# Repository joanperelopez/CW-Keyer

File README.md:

# CW keyer based on K3NG and K5BCQ work

This project was started in April 2023 based in the CW keyer of K3NG. 
I also took advantage of the good work of K5BCQ by incorporating the MEGA2560 processor. My contribution to the project has been very humble: 
  1. I have made a new schematic and PCB with SMD components. 
  2. The incorporation of a 20x4 LCD display.
  3. 3D design of a box for the entire new project.
  4. Galvanic isolation of inputs and outputs. (Optocouplers and audio transformer).
  5. Side tone regulation.
  6. USB interface.

NOTES: All documentation belongs to version 1 of the project. In this version I saw that the volume of the speaker is not very loud and I made some modifications in the 1.2 schematic that are not implemented in the current PCB. If someone wants to add these modifications they can modify the current PCB or, as is my case, add them manually.

Mechanical design made with FreeCAD.

Electronic design made with KICAD.

For download the software, setup and documentation you can go to the author's repository: https://github.com/k3ng/k3ng_cw_keyer

You can consult the K5BCQ's repository for all the information related to the modifications to use the MEGA2560: https://github.com/costonisp/CW-keyer-K3NG-K5BCQ

Feel free to copy or modify this project as long as it is not for commercial purposes.

This is what the finished keyer looks like

Exploded view of all the components of the CW keyer

Exploded view of all the components of the CW keyer

Bottom side of the main PCB

Top side of the main PCB

PCB Top view

PCB Bottom view

https://github.com/user-attachments/assets/0f88c8ea-a7e5-4cd0-9d64-bd676a6b64a1

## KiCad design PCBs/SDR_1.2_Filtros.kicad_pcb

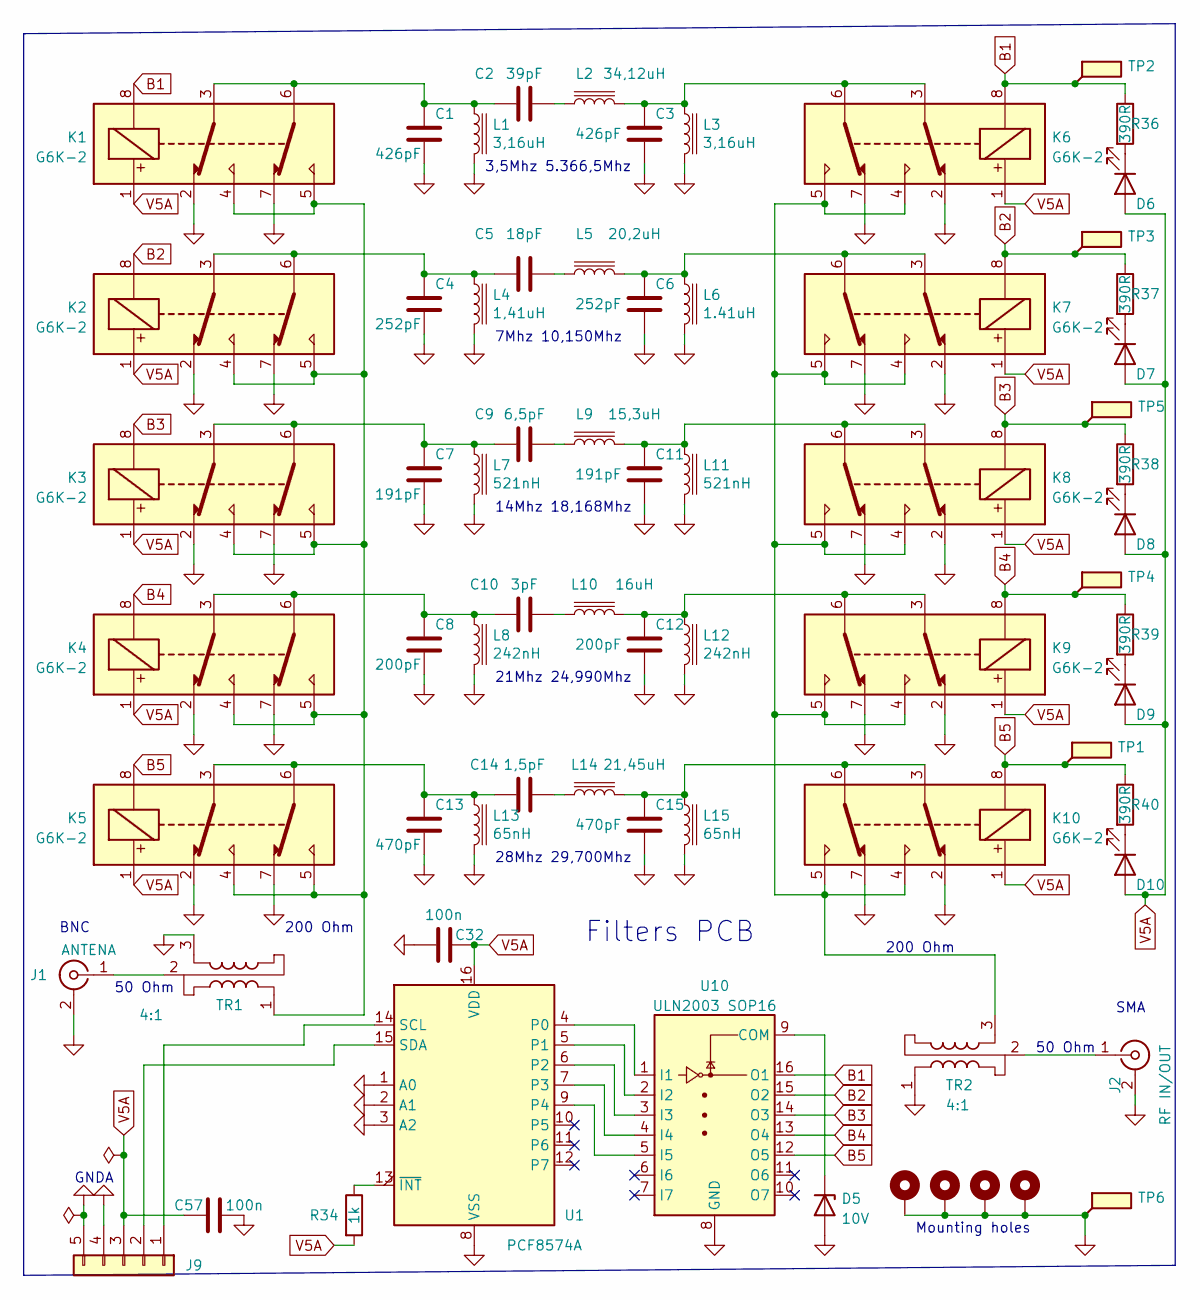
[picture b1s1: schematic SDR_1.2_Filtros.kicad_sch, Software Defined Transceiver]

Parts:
C1: 426pF; LED_0805_2012Metric_Pad1.15x1.40mm_HandSolder
C2: 39pF; C_0805_2012Metric
C3: 426pF; C_0805_2012Metric
C4, C6: 252pF; C_0805_2012Metric
C5: 18pF; C_0805_2012Metric
C7, C11: 191pF; C_0805_2012Metric
C8, C12: 200pF; C_0805_2012Metric
C9: 6,5pF; C_0805_2012Metric
C10: 3pF; C_0805_2012Metric
C13, C15: 470pF; C_0805_2012Metric
C14: 1,5pF; C_0805_2012Metric
C32, C57: 100n; C_0805_2012Metric
D5: 10V; D_SOD-123
D6, D7, D8, D9, D10: LED; LED_0805_2012Metric_Pad1.15x1.40mm_HandSolder
H1, H2, H3, H4: MountingHole_Pad; MountingHole_3.2mm_M3_Pad_TopBottom
J1: ANTENA; BNC_Amphenol_B6252HB-NPP3G-50_Horizontal
J2: RF IN/OUT; SMA_Amphenol_901-144_Vertical
J9: Conn_01x05; JST_EH_B5B-EH-A_1x05_P2.50mm_Vertical
K1, K2, K3, K4, K5, K6, K7, K8, K9, K10: G6K-2; Relay_DPDT_Omron_G6K-2F-Y
L1, L3: 3,16uH; Coil_toroid_T50_Vertical
L2: 34,12uH; Coil_toroid_T50_Vertical
L4: 1,41uH; Coil_toroid_T50_Vertical
L5: 20,2uH; Coil_toroid_T50_Vertical
L6: 1.41uH; Coil_toroid_T50_Vertical
L7, L11: 521nH; Coil_toroid_T50_Vertical
L8, L12: 242nH; Coil_toroid_T50_Vertical
L9: 15,3uH; Coil_toroid_T50_Vertical
L10: 16uH; Coil_toroid_T50_Vertical
L13, L15: 65nH; Coil_toroid_T50_Vertical
L14: 21,45uH; Coil_toroid_T50_Vertical
R34: 1k; R_0805_2012Metric_Pad1.20x1.40mm_HandSolder
R36, R37, R38, R39, R40: 390R; R_0805_2012Metric_Pad1.20x1.40mm_HandSolder
TP1, TP2, TP3, TP4, TP5, TP6: TestPoint_Flag; TestPoint_THTPad_3.0x3.0mm_Drill1.5mm
TR1, TR2: 4:1; TR_4_to_1_T50_Vertical
U1: PCF8574A; SOIC-16W_7.5x10.3mm_P1.27mm
U10: ULN2003 SOP16; SOP-16_3.9x9.9mm_P1.27mm

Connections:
B1: K1.8, K6.8, R36.1, TP2.1, U10.16 (O1)
B2: K2.8, K7.8, R37.1, TP3.1, U10.15 (O2)
B3: K3.8, K8.8, R38.1, TP5.1, U10.14 (O3)
B4: K4.8, K9.8, R39.1, TP4.1, U10.13 (O4)
B5: K5.8, K10.8, R40.1, TP1.1, U10.12 (O5)
GNDA: C1.2, C3.2, C4.2, C6.2, C7.2, C8.2, C11.2, C12.2, C13.2, C15.2, C32.1, C57.1, D5.2 (A), H1.1, H2.1, H3.1, H4.1, J1.2 (Ext), J2.2 (Ext), J9.4, J9.5, K1.2, K1.7, K2.2, K2.7, K3.2, K3.7, K4.2, K4.7, K5.2, K5.7, K6.2, K6.7, K7.2, K7.7, K8.2, K8.7, K9.2, K9.7, K10.2, K10.7, L1.2, L3.2, L4.2, L6.2, L7.2, L8.2, L11.2, L12.2, L13.2, L15.2, TP6.1, TR1.3, TR2.1, U1.1 (A0), U1.2 (A1), U1.3 (A2), U1.8 (VSS), U10.8 (GND); also elsewhere on the board
unnamed: C1.1, C2.2, K1.3, K1.6, L1.1
unnamed: C2.1, L2.1
unnamed: C3.1, K6.3, K6.6, L2.2, L3.1
unnamed: C4.1, C5.2, K2.3, K2.6, L4.1
unnamed: C5.1, L5.1
unnamed: C6.1, K7.3, K7.6, L5.2, L6.1
unnamed: C7.1, C9.2, K3.3, K3.6, L7.1
unnamed: C9.1, L9.1
unnamed: C10.1, L10.1
unnamed: C8.1, C10.2, K4.3, K4.6, L8.1
unnamed: C11.1, K8.3, K8.6, L9.2, L11.1
unnamed: C12.1, K9.3, K9.6, L10.2, L12.1
unnamed: C13.1, C14.2, K5.3, K5.6, L13.1
unnamed: C14.1, L14.1
unnamed: C15.1, K10.3, K10.6, L14.2, L15.1
unnamed: D5.1 (K), U10.9 (COM)
unnamed: D6.1 (K), R36.2
unnamed: D7.1 (K), R37.2
unnamed: D8.1 (K), R38.2
unnamed: D9.1 (K), R39.2
unnamed: D10.1 (K), R40.2
unnamed 27: J1.1 (In), TR1.2; also elsewhere on the board
unnamed: J2.1 (In), TR2.2
unnamed: J9.1, U1.14 (SCL)
unnamed: J9.2, U1.15 (SDA)
unnamed: K1.4, K1.5, K2.4, K2.5, K3.4, K3.5, K4.4, K4.5, K5.4, K5.5, TR1.1
unnamed: K6.4, K6.5, K7.4, K7.5, K8.4, K8.5, K9.4, K9.5, K10.4, K10.5, TR2.3
unnamed: R34.1, U1.13 (~INT)
unnamed: U1.4 (P0), U10.1 (I1)
unnamed: U1.5 (P1), U10.2 (I2)
unnamed: U1.6 (P2), U10.3 (I3)
unnamed: U1.7 (P3), U10.4 (I4)
unnamed: U1.9 (P4), U10.5 (I5)
V5A: C32.2, C57.2, D6.2 (A), D7.2 (A), D8.2 (A), D9.2 (A), D10.2 (A), J9.3, K1.1, K2.1, K3.1, K4.1, K5.1, K6.1, K7.1, K8.1, K9.1, K10.1, R34.2, U1.16 (VDD)

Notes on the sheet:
50 Ohm
GNDA
200 Ohm
Filters PCB
21Mhz 24,990Mhz
3,5Mhz 5.366,5Mhz
28Mhz 29,700Mhz
SMA
14Mhz 18,168Mhz
Mounting holes
BNC
7Mhz 10,150Mhz

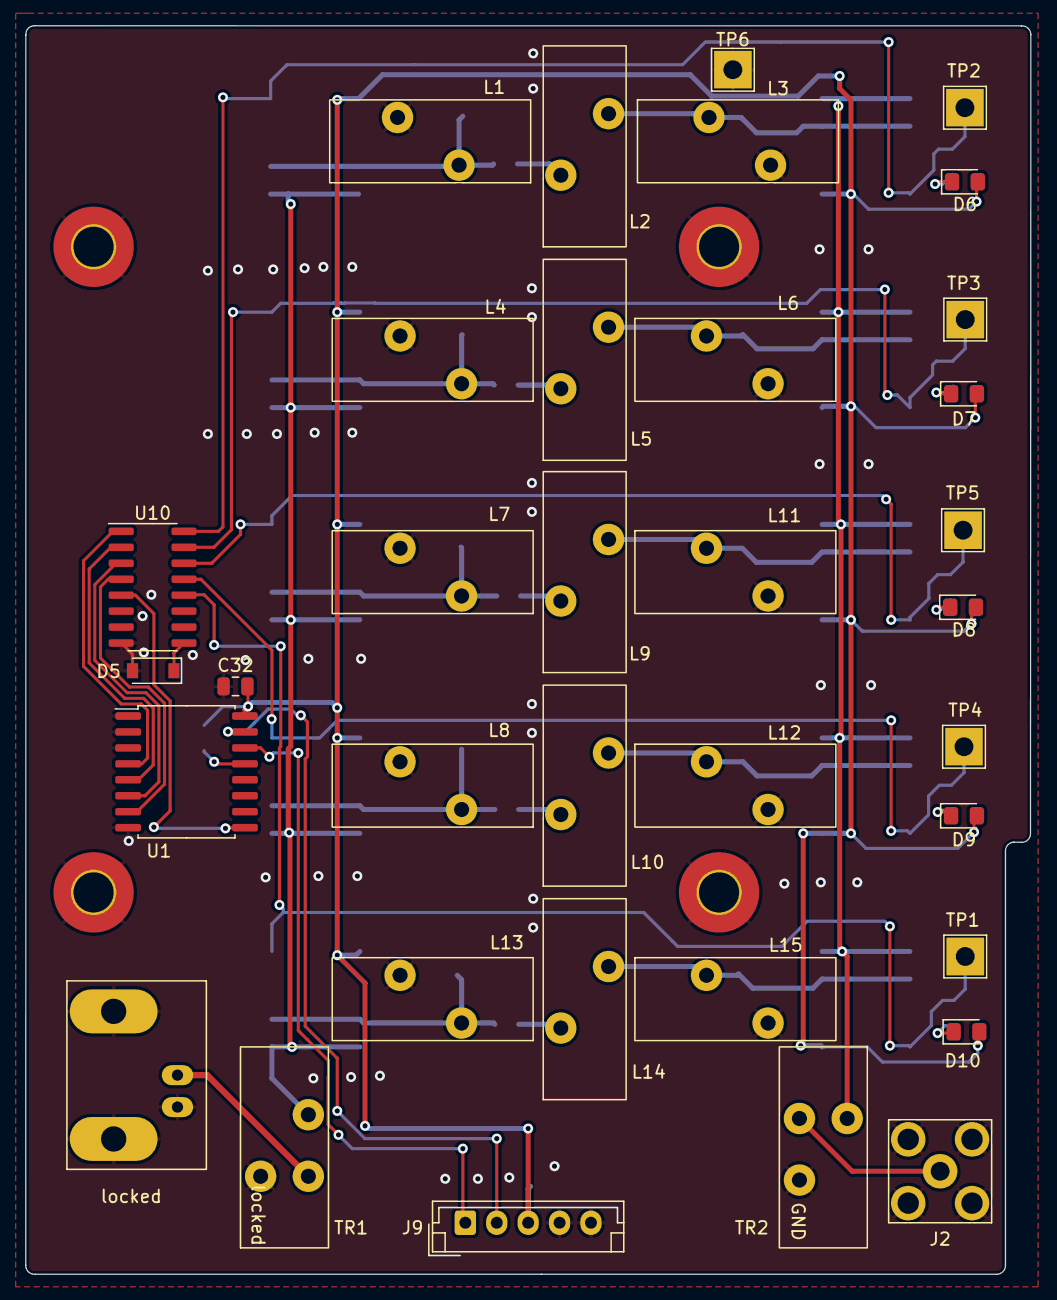
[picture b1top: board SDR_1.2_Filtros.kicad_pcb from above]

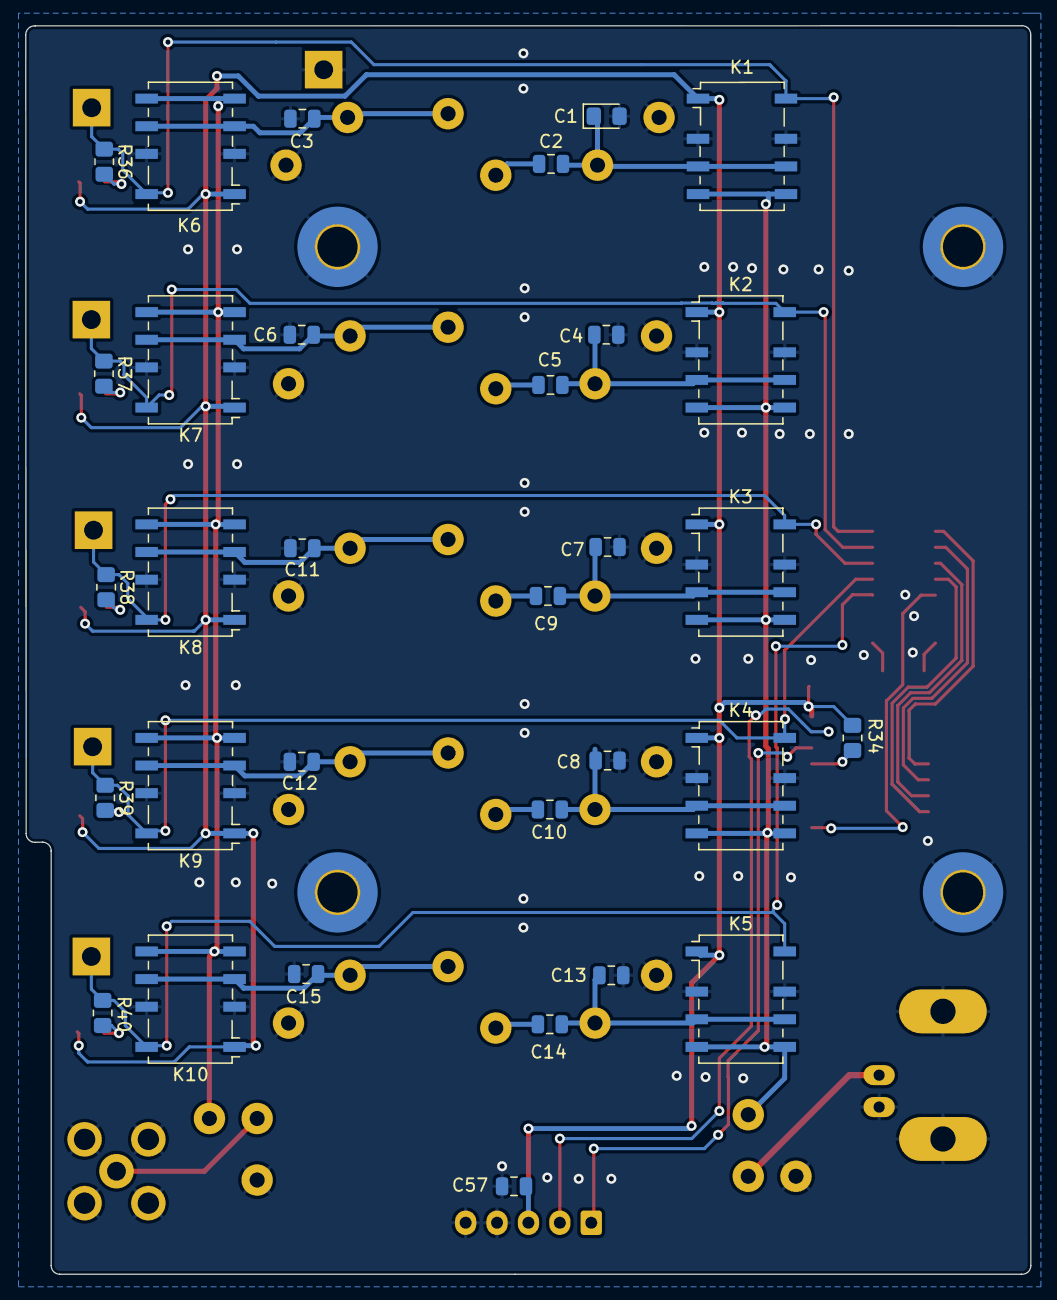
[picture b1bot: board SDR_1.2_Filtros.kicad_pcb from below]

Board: 2 copper layers, 80.0 x 99.4 mm, 71 parts (32 on the bottom side), 40 nets.

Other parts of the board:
locked: ANTENA; BNC_Amphenol_B6252HB-NPP3G-50_Horizontal

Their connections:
GNDA: locked.2 (Ext); also elsewhere on the board
unnamed 27: locked.1 (In); also elsewhere on the board

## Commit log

2025-12-30 Add user attachments link to README
    Added a link for user attachments in the README.
